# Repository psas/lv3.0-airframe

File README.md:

# PSAS Launch Vehicle 3 (LV3) 🚀

This is the repo for the LV3 airframe. This holds everything you need to know about making a rocket out of carbon fiber. This includes CAD files, design and prototyping logs, simulation and testing data, most of all the manufacturing procedures for the carbon fiber airframe modules.  

If you aren't allowed to push, send Joe or Andrew your Github username and ask for access. (This is different from getting added to the PSAS "organization".)

If you're looking to copy or build on this work check out the [doc directory](/doc/), especially the [layup procedure](/doc/mfg/moduleProcedure.md) and please message the people who have committed frequently/recently with any questions (or better yet, [make an issue with your question](https://github.com/psas/lv3.0-airframe/issues)).

If you want some quick physical specifications on the airframe, checkout the [quick facts.](doc/quickFacts.md)
For more detailed info, we have a [model](sim/ORK/LV3_L13.ork) for [OpenRocket](http://openrocket.info/) and a [model](cad/LV3.SLDASM) for [SolidWorks](http://www.solidworks.com/).

## Relevant Repositories
If you want to work on the CAD model, you'll need to have the dependencies cloned to the same directory as this repo. So, something like 

```
PSAS
├── lv3.0-airframe
├── lv3.0-recovery
├── lv3.0-camera-ring
├── lv3.0-umbilical-ring
├── sw-cad-airframe-nsr
└── reaction-control
```

You should also read the [Intro to Git workshop slides](https://drive.google.com/open?id=1pykfwvAw5q1oXGM8aLyhXPHOKDCI61YhK5w33QwzuFw) if you're new to Git
Also, read the [OreSat contributions guide](https://github.com/oresat/oresat-structure/blob/master/.github/CONTRIBUTING.md) if you're new to using SolidWorks with Git.

### Dependencies
* [psas/lv3.0-recovery](https://github.com/psas/lv3.0-recovery) -- CAD and analysis for the eNSR-based recovery system
* [psas/lv3.0-camera-ring](https://github.com/psas/lv3.0-camera-ring) -- 360 degree camera module based on the RunCam Split 2
* [psas/lv3.0-umbilical-ring](https://github.com/psas/lv3.0-umbilical-ring) -- passthrough module for the umbilical and arming switches (uses same format as camera ring)
* [psas/sw-cad-airframe-nsr](https://github.com/psas/sw-cad-airframe-nsr) -- Mechanical separation system for the nosecone/parachute
* [psas/reaction-control](https://github.com/psas/reaction-control) -- Cold gas reaction control system

### Historical
* [psas/LV3-design](https://github.com/psas/LV3-design) -- Early conceptual design of LV3
* [~~psas/mme-capstone~~](https://github.com/psas/mme-capstone) (**DEPRECATED**) -- One of the repositories created durring the 2014 capstone. This contains code for some of the tools they used. 
* [~~psas/sw-cad-carbon-fiber-process~~](https://github.com/psas/sw-cad-carbon-fiber-process) (**DEPRECATED**) -- Yet another repo from the 2014 team. This contains CAD for some of the tools they made.

## TODO:
[Check out the issues list if you're looking for something to do.](https://github.com/psas/lv3.0-airframe/issues) 
Keeping a TODO in the README never works out.

## Project Members
If you're working on the project in any way, please add yourself to this list.

IRL Name                       | Github username        | Current Role
------------------------------ | ---------------------- | ------------
Joe "Rocket Czar" Shields      | @Joedang               | project coordination; MFG; design
Leslie Elwood                  | @lelwood               | MFG; design; logistics
Alex "the Pretty Good" Farias  | @alexkazam             | MFG
Ian Zabel                      | @IanZabel              | cradle design; modelling
Kyle Blakeman                  | @kablakeman            | module sanding
Peter McCloud                  | @petermccloud          | CNC machining
Jorden Rolland                 | @JSRoland              | 
Katia                          | @kp07                  | 
Marie "Marie House" House      | @hmarie2               | anti-lithobreaking precautions
Adam Harris                    | @SaturnVF1             | MFG; manual machining
Josh Carlson                   | @paperman5             | CNC machining; design
Jacob Tiller                   | @JacobTiller           | machining; design
Erin Schmidt                   | @7deeptide             | system integration; design
Nathan Bergey                  | @natronics             | patron saint
Andrew Greenberg               | @andrewgreenberg       | benevolent dictator; pixie wrangler

## What and where
```
|-- cad						holds the Solidworks files for all the machined parts
│   ├── COTS					models for Commercial Off-The-Shelf parts
│   ├── CubeSatAirframeMount			"Cradle" that holds the flight computer (OreSat) inside LV3
|   |-- finCan
|	|-- LongFinFiles			current fin design (flyable and manufacturable)
|   |-- module					files for 18 and 24 inch modules
│   │   ├── jigs				jig for drilling side holes in module rings (and other radial parts)
│   │   └── layup
|   |-- nose					nosecone and mold subassemblies
|   |-- radome					radio-transparent fiberglass module
|   `-- railSled				part for interfacing with the launch rail
│       ├── CAM					G code for the rail sled (obsolete)
│       │   ├── Base
│       │   ├── Neck
│       │   └── Trunk
│       └── Old rail sled designs
|-- doc						all pure documentation
|   |-- aiaa-3.6.1				LaTeX template for AIAA
|   |-- extAbstract				extened abstract for the AIAA paper
|   |-- img					image resources for documentation
|   |-- mfg					step-by-step instructions for manufacturing
|   |-- paper					the conference paper we're submitting to AIAA Space
│   ├── FlightComputerMount			stuff about the Cradle
│   ├── textbook				summary of composite techniques in general
|   `-- updates					bi-monthlyish status updates on the project
|-- sim						simulations and calculations
|   |-- DATCOM					DATCOM cases for cross-validating the design (abandoned)
|   |   |-- case
|   |   |   |-- LV3				case for the LV3 airframe (not complete)
|   |   |   `-- exMiG
|   |   |-- doc					DATCOM documentation
|   |   `-- exlinux				example DATCOM cases
|   |-- ORK					open rocket models
|   |   `-- prev
|   |-- OpenFOAM				CFD models
|   |   `-- LV3\_LD-Haack			model of the 1:5 nose cone
|   |       `-- rcf_100				100-node-long mesh
|   |           |-- 0				initial conditions
|   |           |-- constant			fluid properites
|   |           `-- system			simulation parameters
|   |-- plots					plots of the open rocket data
|   |-- reductions				reductions of the openrocket simulations
|   `-- simData					output of the openrocket simulations
|-- test					data from physical tests on modules
|   `-- profilometer				surface roughness data
│   └── tinyMold				
└── tools					sources/CAD/docs for physical tools used to make LV3
    ├── Composite_Table				the table we do all the layups on
    ├── crusher-control				controller software for one of the crush testers at PSU	
    ├── oven-controller				the temperature controller for the oven
    │   ├── Oven_Controller			the temperature controller for... wait
    │   │   ├── Box				enclosure for the oven controller
    │   │   ├── OvenControl			the temperature contr-- again?!
    │   │   └── oven-controller-master		"A Deja Vu is usually a glitch in the Matrix."
    │   └── src					source code for the controller
    ├── Sheet_Cutting_Templates			templates used to cut sheets of CF, adhesive, et cetera
    └── strain-gauge-amplifier			instrument used to take strain measurements in a crush/tensile test
```

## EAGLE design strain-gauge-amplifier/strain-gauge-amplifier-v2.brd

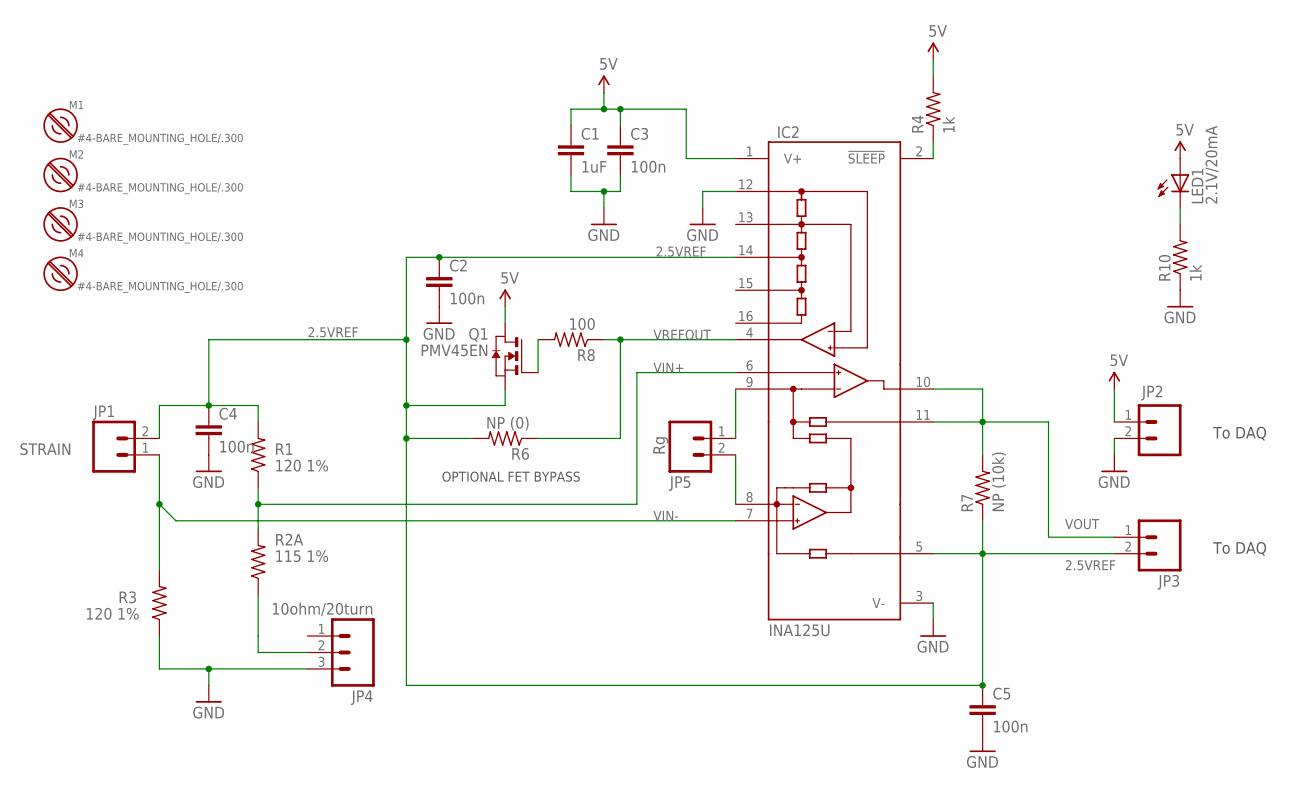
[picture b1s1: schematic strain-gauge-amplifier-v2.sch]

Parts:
C1: 1uF; 0805-C-NOSILK
C2, C3, C4, C5: 100n; 0805-C-NOSILK
IC2: INA125U; SO16-1
JP1: STRAIN; SCREWTERMINAL-5MM-2
JP2, JP3: M025MM; SCREWTERMINAL-5MM-2
JP4: 10ohm/20turn; 1X03_NO_SILK
JP5: Rg; SCREWTERMINAL-5MM-2
LED1: 2.1V/20mA; LED-0603
M1, M2, M3, M4: #4-BARE_MOUNTING_HOLE/.300; #4/.300-BARE+STD_NUT_OR_STAR_WASHER
Q1: PMV45EN; SOT23
R1, R3: 120 1%; 0805-C-NOSILK
R2A: 115 1%; 0805-C-NOSILK
R4, R10: 1k; 0805-C-NOSILK
R6: NP (0); 0805-C-NOSILK
R7: NP (10k); 0805-C-NOSILK
R8: 100; 0805-C-NOSILK

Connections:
2.5VREF: C2.1, C4.1, C5.1, IC2.5 (REF), IC2.14 (REF2.5), JP1.2, JP3.2, Q1.2 (S), R1.2, R6.2, R7.1
5V: C1.1, C3.1, IC2.1 (V+), JP2.1, LED1.A, Q1.3 (D), R4.2
GND: C1.2, C2.2, C3.2, C4.2, C5.2, IC2.3 (V-), IC2.12 (REFCOM), JP2.2, JP4.3, R3.1, R10.1
unnamed: JP4.2, R2A.1
unnamed: IC2.9 (RG), JP5.1
unnamed: IC2.8 (RG), JP5.2
unnamed: Q1.1 (G), R8.2
unnamed: IC2.2 (!SLEEP), R4.1
unnamed: LED1.C, R10.2
VIN+: IC2.6 (+IN), R1.1, R2A.2
VIN-: IC2.7 (-VIN), JP1.1, R3.2
VOUT: IC2.10 (OUT), IC2.11 (SENSE), JP3.1, R7.2
VREFOUT: IC2.4 (REFOUT), R6.1, R8.1

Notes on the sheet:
OPTIONAL FET BYPASS
To DAQ

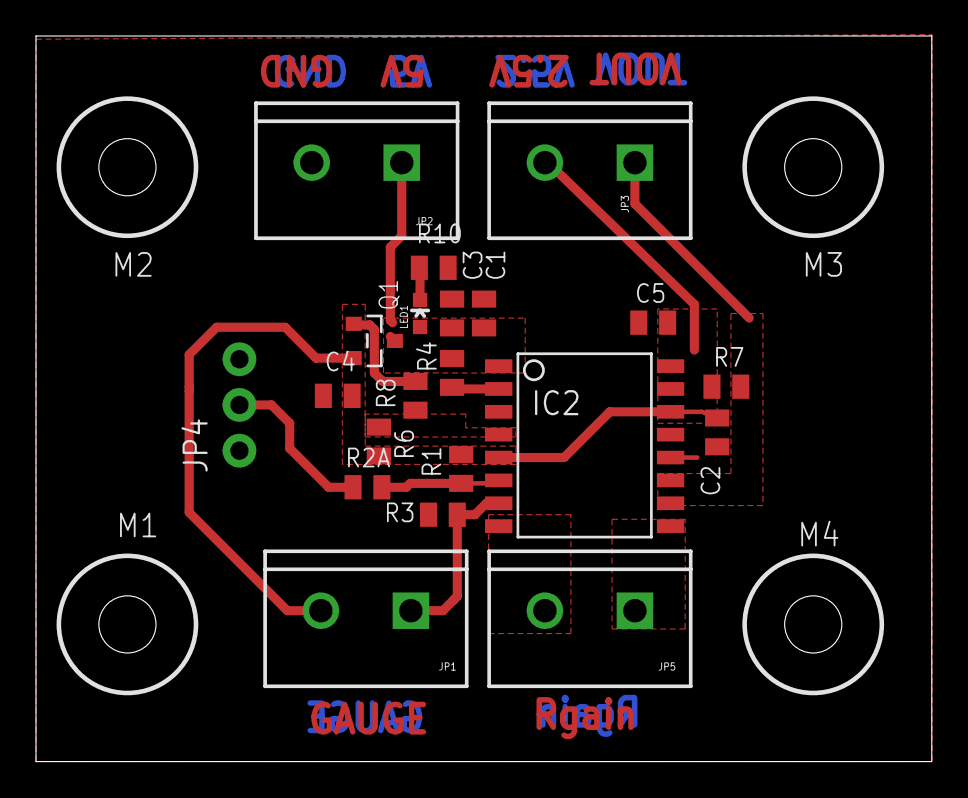
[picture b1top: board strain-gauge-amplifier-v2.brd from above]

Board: 2 copper layers, 49.8 x 40.3 mm, 25 parts (0 on the bottom side), 13 nets.

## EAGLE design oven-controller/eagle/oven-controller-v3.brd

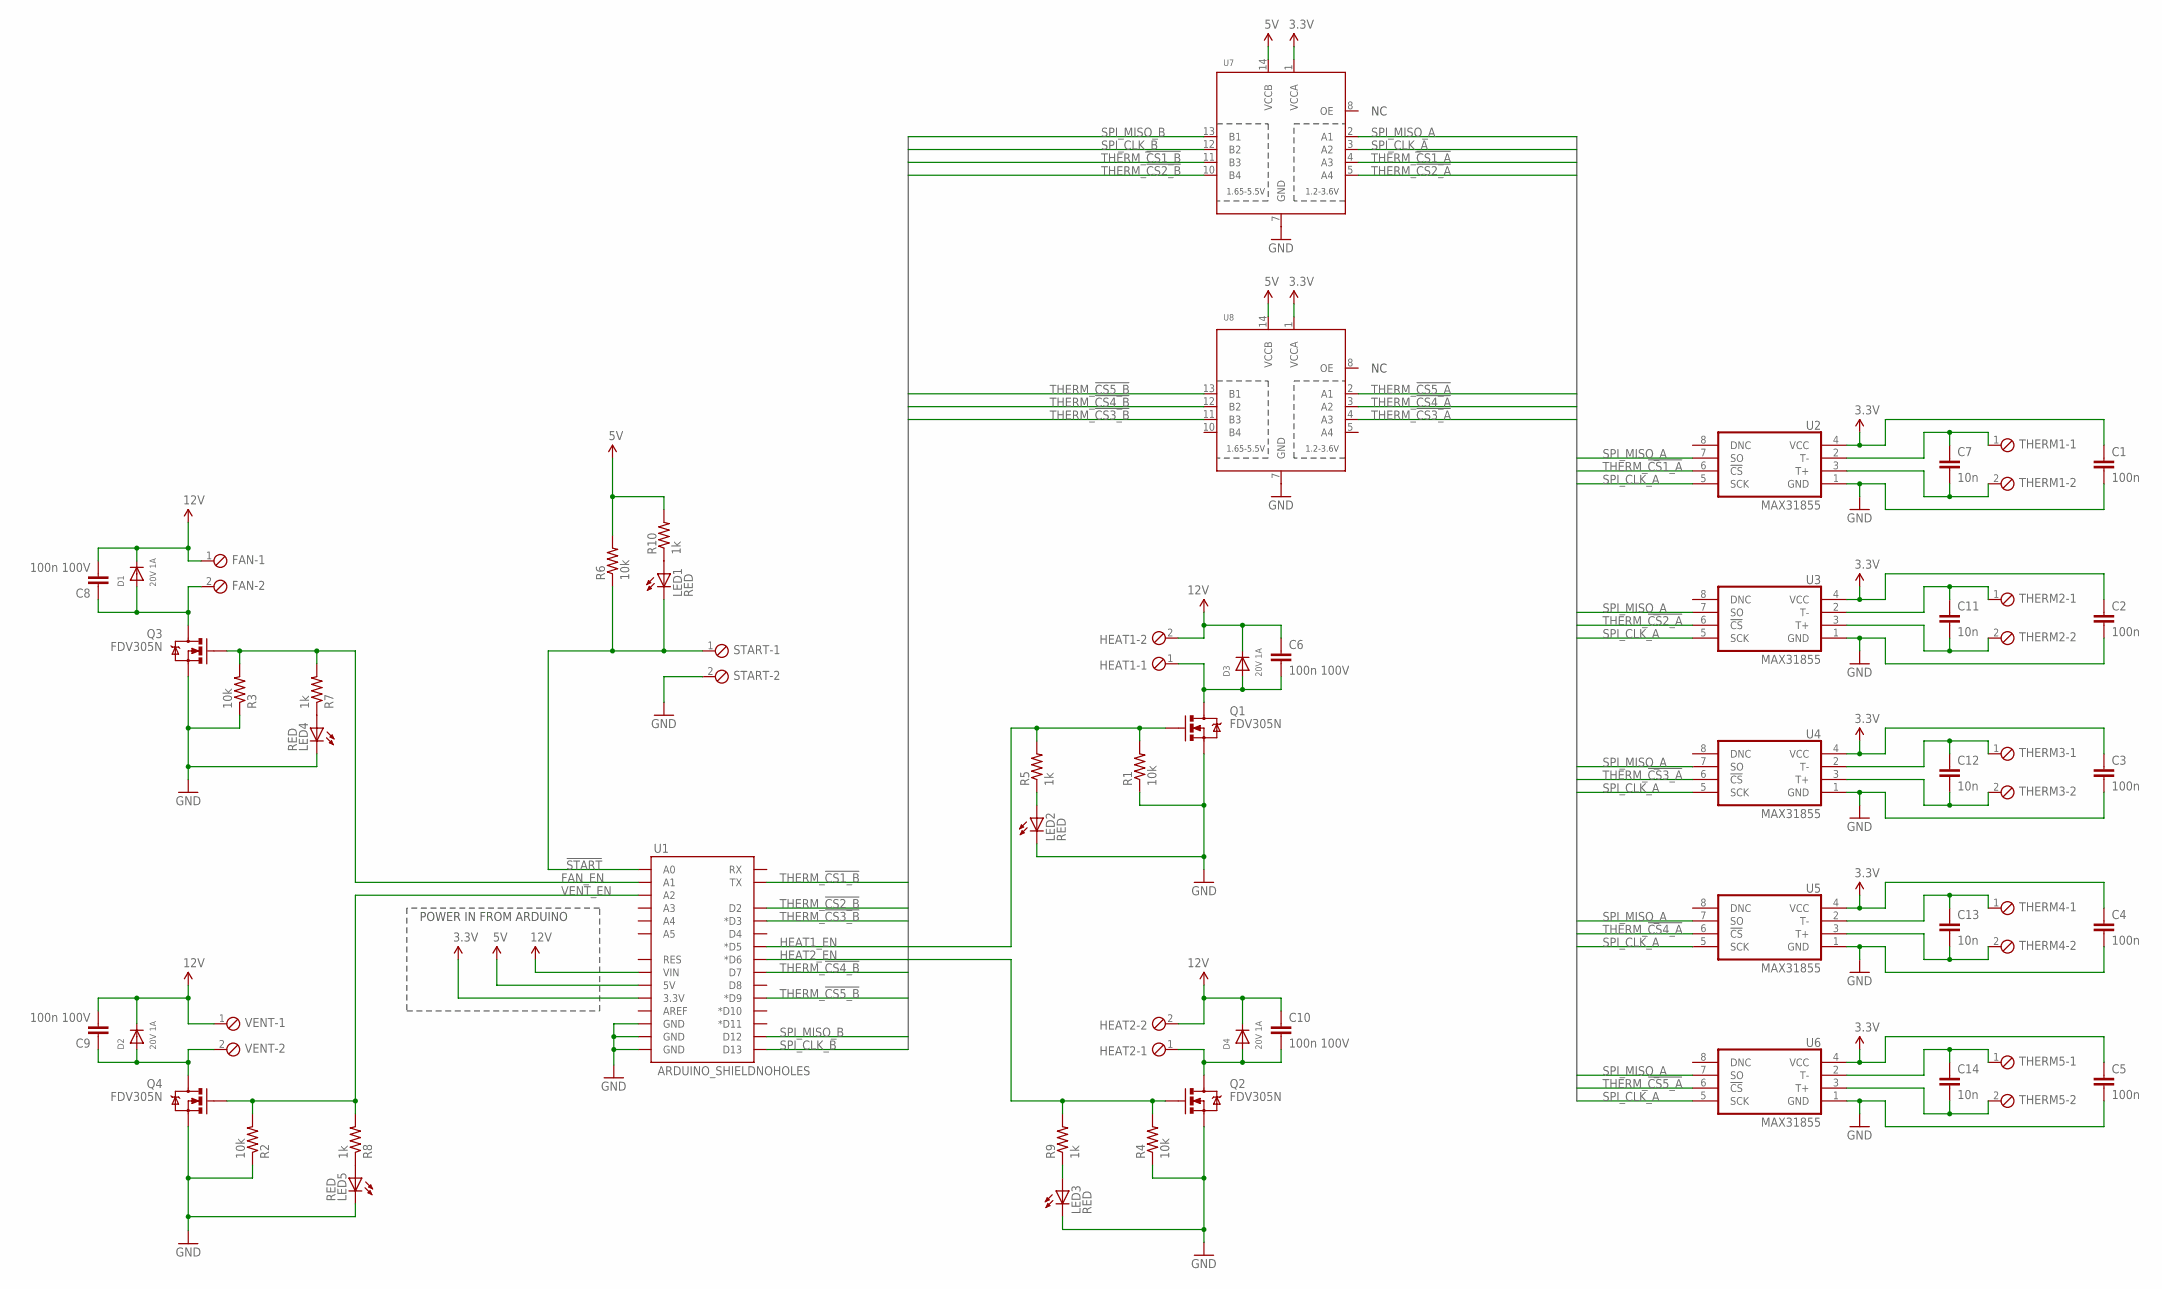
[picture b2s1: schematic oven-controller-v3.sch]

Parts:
C1, C2, C3, C4, C5: 100n; C0603K
C6, C8, C9, C10: 100n 100V; C0603K
C7, C11, C12, C13, C14: 10n; C0603K
D1, D2, D3, D4: 20V 1A; DO-214AC-SMA
FAN: MPT2; 2POL254
HEAT1, HEAT2: MPT2; 2POL254
LED1, LED2, LED3, LED4, LED5: RED; LED-0603
Q1, Q2, Q3, Q4: FDV305N; SOT23-3
R1, R2, R3, R4, R6: 10k; 0603-C-NOSILK
R5, R7, R8, R9, R10: 1k; 0603-C-NOSILK
START: MPT2; 2POL254
THERM1, THERM2, THERM3, THERM4, THERM5: MPT2; 2POL254
U1: ARDUINO_SHIELDNOHOLES; DUEMILANOVE_SHIELD_NOHOLES
U2, U3, U4, U5, U6: MAX31855; SO-8
U7, U8: TXB0104PWR; TSSOP14
VENT: MPT2; 2POL254

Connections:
3.3V: C1.1, C2.1, C3.1, C4.1, C5.1, U1.3.3V, U2.4 (VCC), U3.4 (VCC), U4.4 (VCC), U5.4 (VCC), U6.4 (VCC), U7.1 (VCCA), U7.8 (OE), U8.1 (VCCA), U8.8 (OE)
5V: R6.2, R10.2, U1.5V, U7.14 (VCCB), U8.14 (VCCB)
12V: C6.1, C8.2, C9.2, C10.1, D1.C, D2.C, D3.C, D4.C, FAN.1, HEAT1.2, HEAT2.2, U1.VIN, VENT.1
!START: LED1.C, R6.1, START.1, U1.A0
FAN_EN: Q3.1 (G), R3.2, R7.2, U1.A1
GND: C1.2, C2.2, C3.2, C4.2, C5.2, LED2.C, LED3.C, LED4.C, LED5.C, Q1.2 (S), Q2.2 (S), Q3.2 (S), Q4.2 (S), R1.1, R2.1, R3.1, R4.1, START.2, U1.GND@0 (GND), U1.GND@1 (GND), U1.GND@2 (GND), U2.1 (GND), U3.1 (GND), U4.1 (GND), U5.1 (GND), U6.1 (GND), U7.7 (GND), U8.7 (GND)
HDR3: C8.1, D1.A, FAN.2, Q3.3 (D)
HEAT1_EN: Q1.1 (G), R1.2, R5.2, U1.D5 (*D5)
HEAT2_EN: Q2.1 (G), R4.2, R9.2, U1.D6 (*D6)
unnamed: LED1.A, R10.1
unnamed: C7.1, THERM1.1, U2.2 (T-)
unnamed: C9.1, D2.A, Q4.3 (D), VENT.2
unnamed: C6.2, D3.A, HEAT1.1, Q1.3 (D)
unnamed: C7.2, THERM1.2, U2.3 (T+)
unnamed: C13.1, THERM4.1, U5.2 (T-)
unnamed: LED2.A, R5.1
unnamed: C13.2, THERM4.2, U5.3 (T+)
unnamed: LED4.A, R7.1
unnamed: C12.1, THERM3.1, U4.2 (T-)
unnamed: C11.1, THERM2.1, U3.2 (T-)
unnamed: C11.2, THERM2.2, U3.3 (T+)
unnamed: C14.2, THERM5.2, U6.3 (T+)
unnamed: C14.1, THERM5.1, U6.2 (T-)
unnamed: LED3.A, R9.1
unnamed: LED5.A, R8.1
unnamed: C12.2, THERM3.2, U4.3 (T+)
unnamed: C10.2, D4.A, HEAT2.1, Q2.3 (D)
SPI_CLK_A: U2.5 (SCK), U3.5 (SCK), U4.5 (SCK), U5.5 (SCK), U6.5 (SCK), U7.3 (A2)
SPI_CLK_B: U1.D13, U7.12 (B2)
SPI_MISO_A: U2.7 (SO), U3.7 (SO), U4.7 (SO), U5.7 (SO), U6.7 (SO), U7.2 (A1)
SPI_MISO_B: U1.D12, U7.13 (B1)
THERM_!CS1_A: U2.6 (!CS), U7.4 (A3)
THERM_!CS1_B: U1.TX, U7.11 (B3)
THERM_!CS2_A: U3.6 (!CS), U7.5 (A4)
THERM_!CS2_B: U1.D2, U7.10 (B4)
THERM_!CS3_A: U4.6 (!CS), U8.4 (A3)
THERM_!CS3_B: U1.D3 (*D3), U8.11 (B3)
THERM_!CS4_A: U5.6 (!CS), U8.3 (A2)
THERM_!CS4_B: U1.D7, U8.12 (B2)
THERM_!CS5_A: U6.6 (!CS), U8.2 (A1)
THERM_!CS5_B: U1.D9 (*D9), U8.13 (B1)
VENT_EN: Q4.1 (G), R2.2, R8.2, U1.A2

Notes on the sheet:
POWER IN FROM ARDUINO

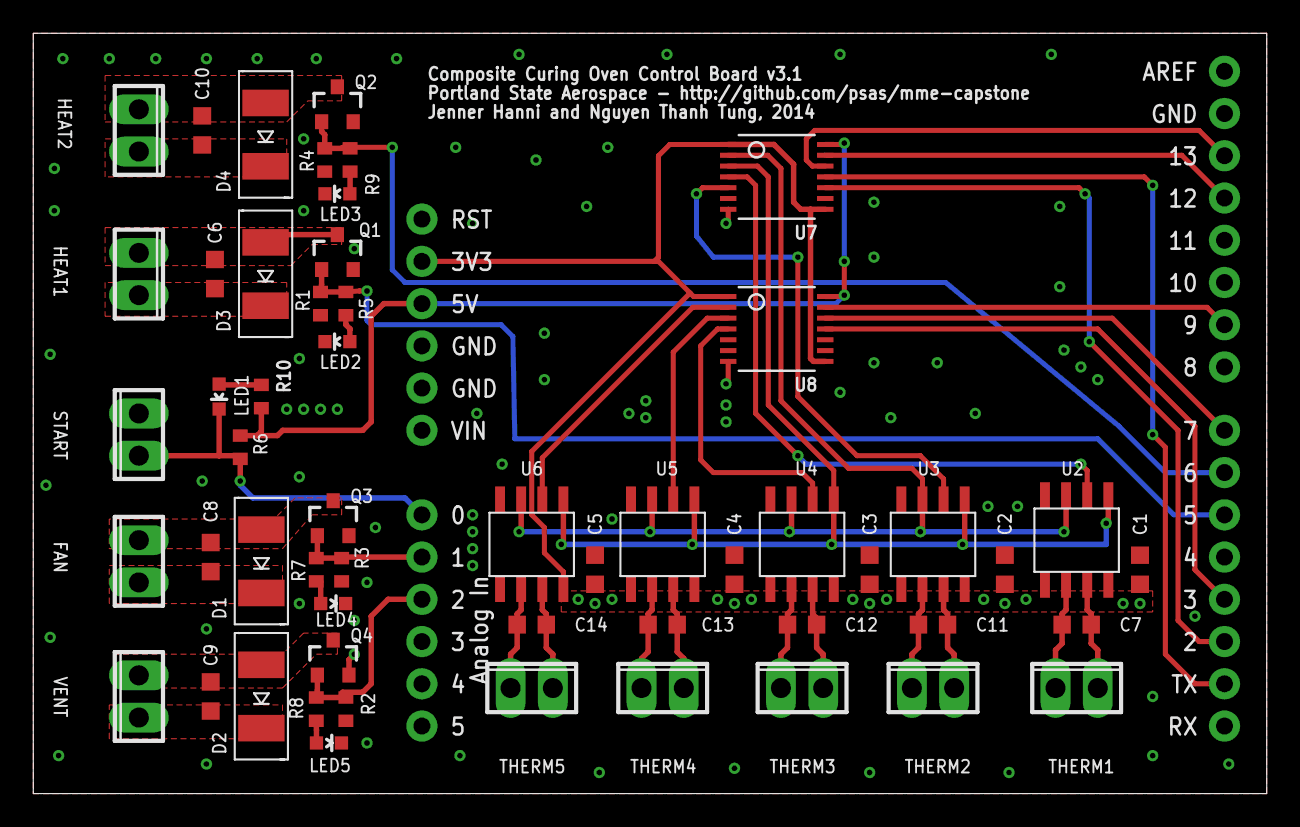
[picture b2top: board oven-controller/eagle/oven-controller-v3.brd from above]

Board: 2 copper layers, 74.2 x 45.7 mm, 55 parts (0 on the bottom side), 42 nets.

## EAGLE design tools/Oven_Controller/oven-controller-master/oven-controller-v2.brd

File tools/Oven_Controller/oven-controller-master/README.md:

oven-controller
===============

For the composites oven team at Portland State. 

v0 - the original schematic representation of the current working breadboard setup.

v1 - the finished Arduino shield version on a printed circuit board. this works! 

v2 - additions to the v1 Arduino shield design

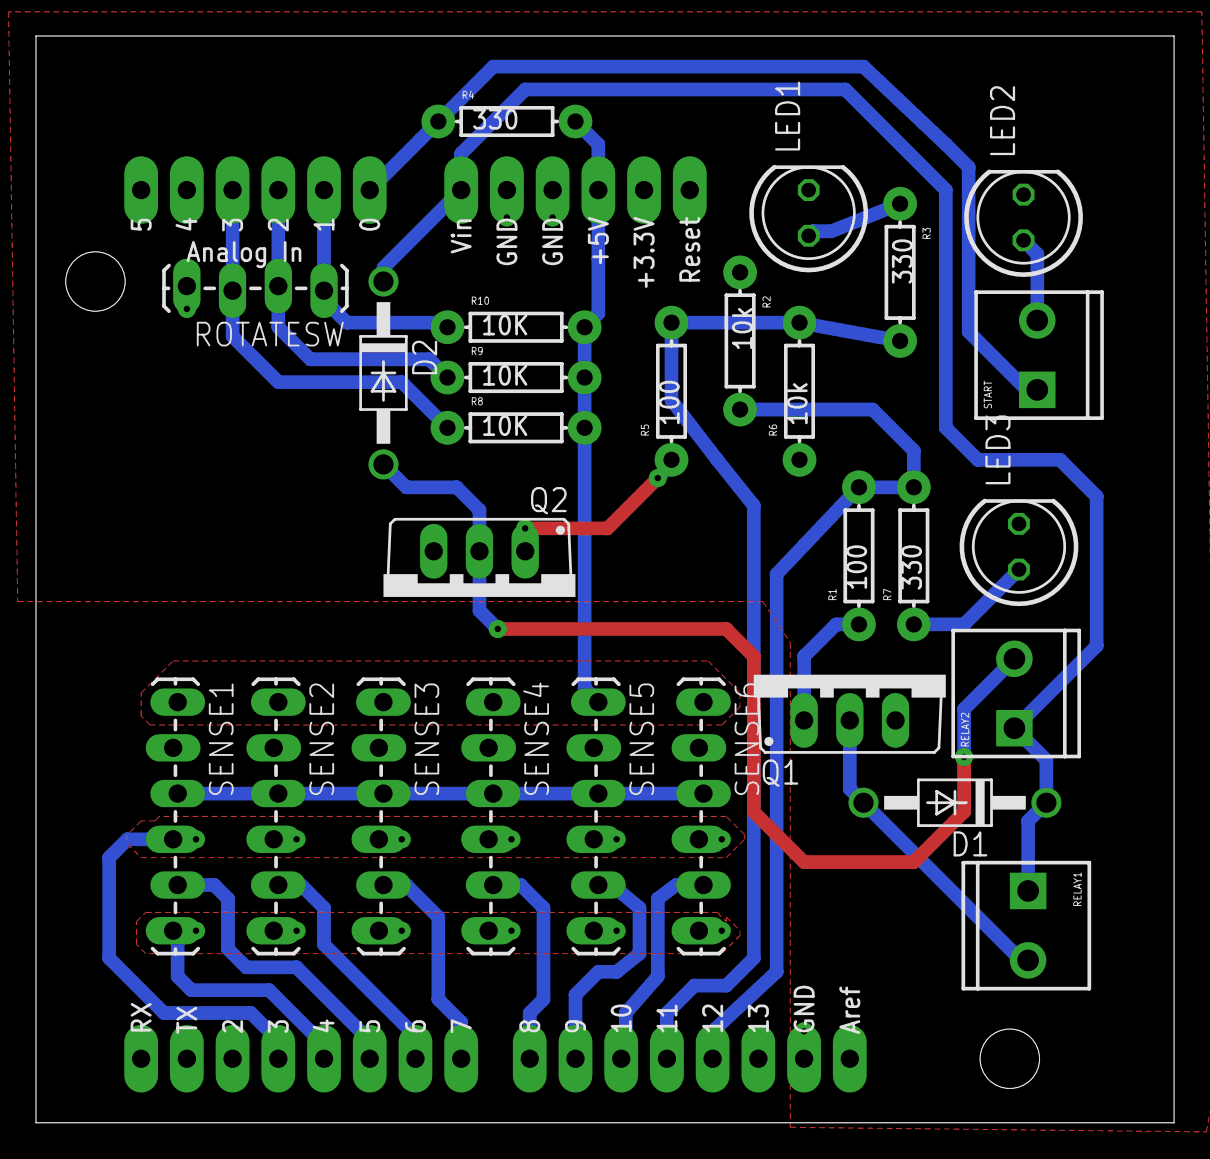
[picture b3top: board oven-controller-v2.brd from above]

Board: 2 copper layers, 63.2 x 60.4 mm, 28 parts (0 on the bottom side), 24 nets.

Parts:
D1, D2: 1N4942; DO41-10
LED1, LED2, LED3: RED; LED5MM
Q1, Q2: IRFL310; TO220BV
R1, R5: 100; AXIAL-0.3
R2, R6: 10k; AXIAL-0.3
R3, R4, R7: 330; AXIAL-0.3
R8, R9, R10: 10K; AXIAL-0.3
RELAY1: RL1; SCREWTERMINAL-3.5MM-2_LOCK
RELAY2: RL2; SCREWTERMINAL-3.5MM-2_LOCK
ROTATESW: SW; 1X04_LOCK_LONGPADS
SENSE1, SENSE2, SENSE3, SENSE4, SENSE5, SENSE6: 1X06_LOCK_LONGPADS
START: SCREWTERMINAL-3.5MM-2_LOCK
U1: ARDUINO_SHIELDLONGPADS; DUEMILANOVE_SHIELD_LONGPADS

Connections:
5V: R4.P$2, R8.P$2, R9.P$2, R10.P$2, SENSE1.1, SENSE2.1, SENSE3.1, SENSE4.1, SENSE5.1, SENSE6.1, U1.5V
A0: R4.P$1, START.1, U1.A0
A1: R10.P$1, ROTATESW.1, U1.A1
A2: R9.P$1, ROTATESW.2, U1.A2
A3: R8.P$1, ROTATESW.3, U1.A3
CCO: SENSE1.4, SENSE2.4, SENSE3.4, SENSE4.4, SENSE5.4, SENSE6.4, U1.D3
CS_PIN5: SENSE1.5, U1.D5
CS_PIN6: SENSE2.5, U1.D6
CS_PIN7: SENSE3.5, U1.D7
CS_PIN8: SENSE4.5, U1.D8
CS_PIN9: SENSE5.5, U1.D9
CS_PIN10: SENSE6.5, U1.D10
CS_PIN11: R3.P$2, R5.P$2, R6.P$2, U1.D11
CS_PIN12: R1.P$2, R2.P$2, R7.P$2, U1.D12
GND: LED1.K, LED2.K, LED3.K, Q1.S, Q2.S, R2.P$1, R6.P$1, ROTATESW.4, SENSE1.3, SENSE2.3, SENSE3.3, SENSE4.3, SENSE5.3, SENSE6.3, U1.GND@0, U1.GND@1, U1.GND@2
unnamed: Q2.G, R5.P$1
unnamed: Q1.G, R1.P$1
unnamed: D1.A, Q1.D, RELAY1.2
unnamed: D2.A, Q2.D, RELAY2.2
unnamed: LED1.A, R3.P$1
unnamed: LED3.A, R7.P$1
unnamed: LED2.A, START.2
SCLK_PIN4: SENSE1.6, SENSE2.6, SENSE3.6, SENSE4.6, SENSE5.6, SENSE6.6, U1.D4
VIN: D1.C, D2.C, RELAY1.1, RELAY2.1, U1.VIN

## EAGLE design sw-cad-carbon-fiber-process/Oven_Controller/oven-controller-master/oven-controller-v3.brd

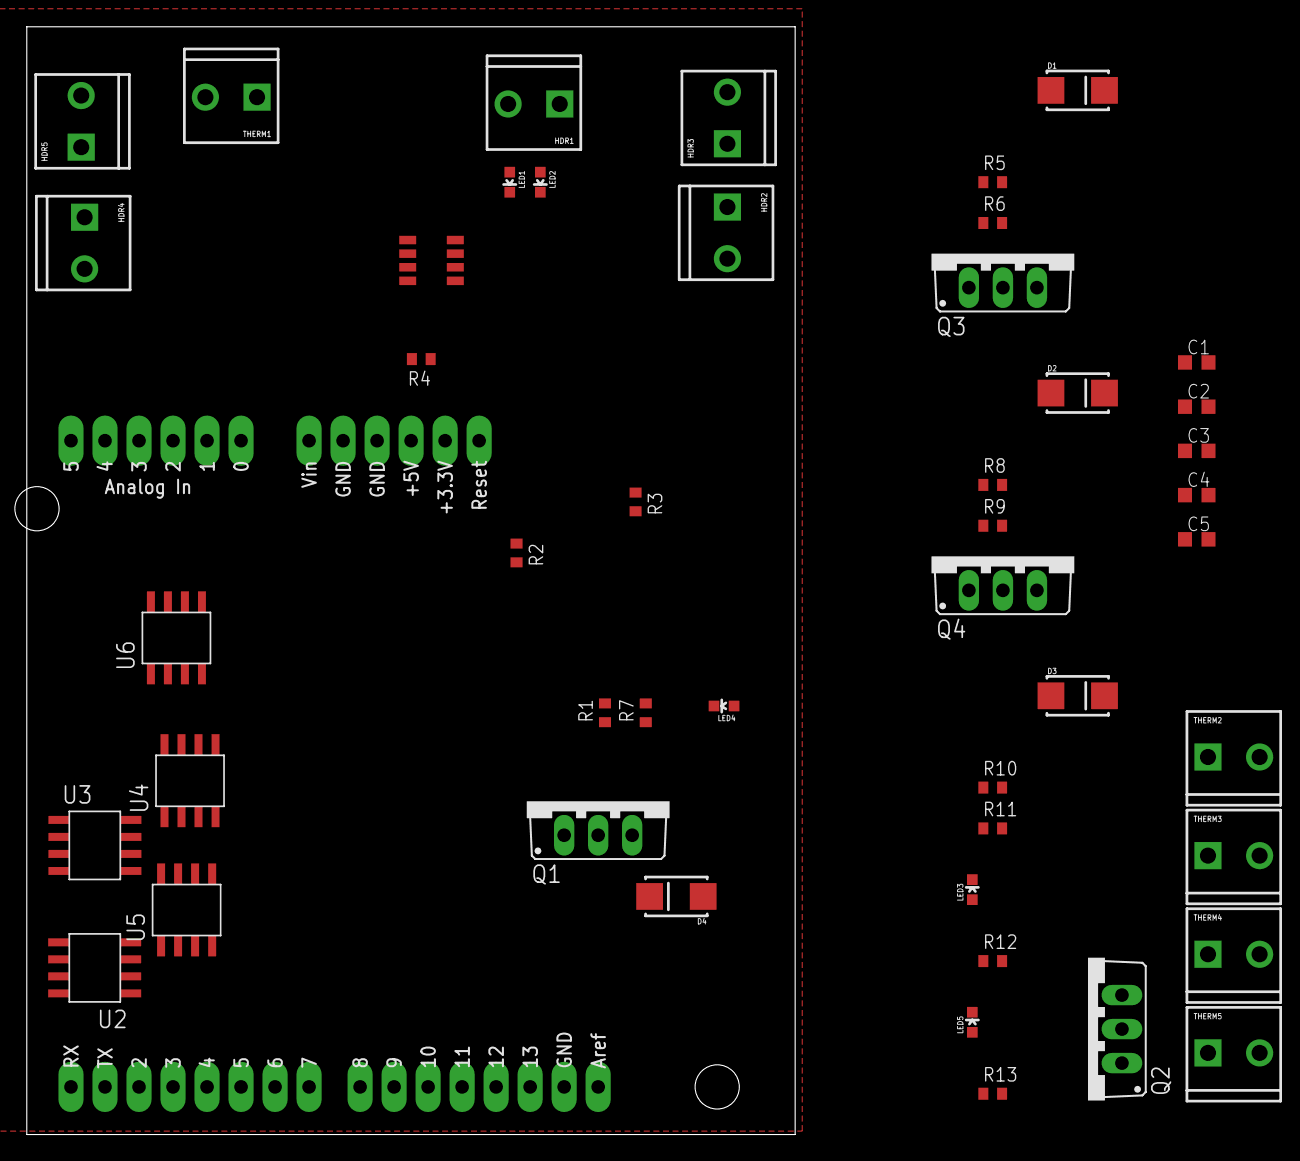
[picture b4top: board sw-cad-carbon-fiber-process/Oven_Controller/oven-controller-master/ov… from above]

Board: 2 copper layers, 57.4 x 82.7 mm, 48 parts (0 on the bottom side), 39 nets, no tracks yet.

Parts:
C1, C2, C3, C4, C5: C0603K
D1, D2, D3, D4: RS1DB-13-F; SMA-DIODE_ALT
HDR1: SCREWTERMINAL-3.5MM-2_LOCK
HDR2: HEAT1; SCREWTERMINAL-3.5MM-2_LOCK
HDR3: HEAT2; SCREWTERMINAL-3.5MM-2_LOCK
HDR4: FAN; SCREWTERMINAL-3.5MM-2_LOCK
HDR5: VENT; SCREWTERMINAL-3.5MM-2_LOCK
LED1, LED2, LED3, LED4, LED5: RED; LED-0603
Q1, Q2, Q3, Q4: IRFL310; TO220BV
R1, R5, R8, R10: 100; 0603-C-NOSILK
R2, R6, R9, R11: 10k; 0603-C-NOSILK
R3, R4, R7, R12, R13: 330; 0603-C-NOSILK
THERM1, THERM2, THERM3, THERM4, THERM5: SCREWTERMINAL-3.5MM-2_LOCK
U1: ARDUINO_SHIELDLONGPADS; DUEMILANOVE_SHIELD_LONGPADS
U2, U3, U4, U5, U6: MAX31855; SO-8
U7: SN74LVC1G139; 8LSSOP

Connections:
3.3V: C1.1, C2.1, C3.1, C4.1, C5.1, U1.3.3V, U2.4, U3.4, U4.4, U5.4, U6.4
5V: R4.2, U1.5V, U7.P$8
12V: D1.C, D2.C, D3.C, D4.C, HDR2.1, HDR3.1, HDR4.1, HDR5.1, U1.VIN
CS_FAN: R7.2, R10.2, R11.2, U7.P$5
CS_HEAT1: R3.2, R5.2, R6.2, U7.P$7
CS_HEAT2: R8.2, R9.2, R12.2, U7.P$6
CS_VENT: R1.2, R2.2, R13.2, U7.P$3
GND: C1.2, C2.2, C3.2, C4.2, C5.2, LED1.C, LED2.C, LED3.C, LED4.C, LED5.C, Q1.S, Q2.S, Q3.S, Q4.S, R2.1, R6.1, R9.1, R11.1, U1.GND@0, U1.GND@1, U1.GND@2, U2.1, U3.1, U4.1, U5.1, U6.1, U7.P$4
HDR3: D3.A, HDR4.2, Q4.D
unnamed: Q2.G, R5.1
unnamed: Q1.G, R1.1
unnamed: D4.A, HDR5.2, Q1.D
unnamed: D1.A, HDR2.2, Q2.D
unnamed: THERM1.1, U2.2
unnamed: THERM1.2, U2.3
unnamed: LED2.A, R3.1
unnamed: THERM2.1, U3.2
unnamed: LED4.A, R7.1
unnamed: HDR1.2, LED1.A
unnamed: THERM2.2, U3.3
unnamed: THERM3.1, U4.2
unnamed: THERM3.2, U4.3
unnamed: THERM4.1, U5.2
unnamed: THERM4.2, U5.3
unnamed: THERM5.1, U6.2
unnamed: THERM5.2, U6.3
unnamed: LED3.A, R12.1
unnamed: LED5.A, R13.1
unnamed: Q3.G, R8.1
unnamed: D2.A, HDR3.2, Q3.D
unnamed: Q4.G, R10.1
RELAY_MUX_SEL1: U1.D5, U7.P$1
RELAY_MUX_SEL2: U1.D6, U7.P$2
START: HDR1.1, R4.1, U1.A0
THERM_CS1: U1.TX, U2.6
THERM_CS2: U1.D2, U3.6
THERM_CS3: U1.D3, U4.6
THERM_CS4: U1.D7, U5.6
THERM_CS5: U1.D9, U6.6

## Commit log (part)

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2016-02-25 added to Significance and Plan of Work
2016-02-25 removed reference to other teams using PSAS designs
2016-03-04 added nose heating analysis script
2016-03-13 optimized spline point placement
    This script is meant to find the optimal placement of an extra spline point for the LV3 nose cone. The curvature of the LD-Haack shape near the tip creates a large error when using evenly distributed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
2016-03-30 Experimented with fin shapes. Started DATCOM input.
2016-03-31 Added neutrally stable fin design.
2016-03-31 added very rough model for L13b
2016-04-01 output files for the MiG-17 case
2016-04-01 silly to have huge DATCOM source messing up commit logs
2016-04-01 updated description
2016-04-03 added symmetrical fin version
2016-04-12 fixed wrong image name
2016-04-12 wrote more of the update, added images
2016-04-15 finished writing the "weekly" update
2016-04-15 minor edits to the weekly update
2016-05-09 wrote another update
2016-05-20 added directory for AIAA paper, and did some prep
2016-05-23 profilometer stuff; will add other data soon.
2016-05-26 added a CoP compensation design that uses 4 fins (not worth it)
    The apogee is basically the same and it uses an extra fin. There's not
    much point to this.
2016-06-11 Wrote the fin layup procedure; modified cylinder layup
    The fin procedure still needs images. The cylinder layup needs updated
    images.
2016-06-15 slight documentation reorganization
2016-06-16 fixed to-do list formatting
2016-06-18 Update README.md
    My apologies for the mess. I was just practicing different things from a work computer and I didn't realize it was creating a problem (?).
2016-06-22 Cleared out the old cad files
2016-06-23 Readme: Clean up some markup for readability.
2016-07-06 Changed material definition; modified truss size; added composite thickness
2016-07-07 Added fillet, updated drag force, applied mesh control, next step: weight reduction
2016-07-11 added pics for layup tutorial and mold sealing
2016-07-16 Added new new fin design with slot for leading edge material
2016-07-19 Added temp markdown for flutter velocity calculation
2016-07-20 modified nose mold to accommodate recovery system
    increased the cylindrical section from 2 in to 8 in
    increased the nose hole diameter to 1 in
    made a slight change in the defining dimensions of the nose tip
2016-07-25 Strengthened front/back of mold; added index holes; added a ruler
2016-07-29 most of the modifications requested by Alex Chally
    still need to add indexing holes, fixturing holes, and optional flange
    holes
2016-07-30 Updated the fin CAD
2016-07-30 found a *good* solution to show the analysis
    ... after a lot of fighting with pandoc ;_;
2016-07-30 updated the model, as per Allex Chally's requests
2016-08-02 added descriptions on open-source software used
2016-08-03 added crush data for LU16-20 (fiberglass module)
2016-08-03 renamed the crush analysis; added the plots
2016-08-08 Added to the nose cone section
2016-08-09 added BOM from 2014 version
2016-08-12 description of the basic design and bibliography
    Next:
    add diagram/picture of the sandwich design;
    add more detailed description of the modules
    add pictures of the compressive failure
    add pictures of the puncture failure
    add CAD render of the cylindrical modules and/or whole rocket (this
2016-08-14 added materials and module sections, layer diagram
    Next:
    add pictures of descructive testing
    add picture of layers, put alongside diagram
    add picture/model of module
    write section on destructive testing
    add plot of surface features
2016-08-16 Add to aquire and nose cone 8/15
2016-08-17 some figure fixes
    Also checking to see if my local copy still points to the remote one
2016-08-18 some figure changes; changed testing and nose cone
2016-08-18 condensed NC and MAT sections; moved figures
2016-08-18 merged redundant paragraphs
2016-08-18 PSAS is plans -> PSAS' plans
2016-08-19 Updated sheet metal model; Edited assembly
2016-08-24 Updated old assembly, added polycarbonate model
2016-08-27 Added LV3 fin jigs
2016-08-30 Updated plexi assembly; Created necessary components and assembly
2016-09-02 Updated acrylic model; Added drawings; Added telem placeholder
2016-09-07 added some pics of the taping/bagging process
2016-09-08 This piece attaches the cubesat cradle to the module rings.
2016-09-08 found a decent way to get tables into Inkscape
2016-09-09 added plots to the poster
2016-09-09 added dummy text and did some alignment tweaking
2016-09-10 Added end plate laser cutting sheet
2016-09-10 added actual text; changed QR codes; tweaked fonts
2016-09-12 Added more exposition and updated requirements.
2016-09-13 Updated requirements text
2016-09-25 Technical drawing for nose cone tip.
2016-09-27 added MasterCAM coordinate system to the model
2016-09-28 Added even more laser cutting files; Added the new rail to be cut
2016-10-10 Created sim assembly and part, performed static torsion sim
2016-10-12 Updated V2 Assem; Included V2 CubeSat (2U); Modified Interface ring for strength and weight
2016-10-18 updated README; created SLDPRT of a test mold
2016-10-20 Updated middle fin jig technical drawing
2016-10-24 Made a technical drawing for the top/bottom fin jigs
2016-11-07 added initial files for fin CAM
2016-12-13 Updated mid fin jig drawing and redid top/bottom fin jig drawing
2016-12-18 added the RCS ring to the main assembly
    Still need to add :
    * guts for the RCS
    * guts for the eNSR
    * recovery system
    * motor
    We (PSAS) should also try to figure out some way of saving our SW
2016-12-21 Updated fin jig drawings to be more standardized
2017-01-10 possible geometry for the big mold
    used to make a negative mold with carbon fiber
2017-01-10 updated BOM to 2016 version
2017-01-13 Updated README to provide suggested reading.
2017-02-09 added images of the layup process and the molds
    I also made a python script to convert images to a smaller size.
    If an image is larger than 500 pickles in both dimensions, it
    rescales the image to be 500 pickles in the smallest dimension.
    That should be a bit easier than doing each one in GIMP.
2017-02-13 updated module MFG procedure and README
2017-02-22 added relevant repos to README
2017-02-25 extra debugging to the serial monitor
2017-02-27 added picture and video of the nosecone mold layup
2017-03-27 small tweaks to the tip drawing
2017-03-28 Updated TODO
2017-03-30 tweaked coordinate system
2017-03-30 technical drawing for the fin jig baseplate
2017-04-05 assemblies/parts for making/using nosecone mold
2017-04-06 created technical drawing of the sled jig
2017-04-11 created drawing of male coupling ring
2017-04-11 explanatory drawing of how internals mount to LV3
    Needs screws!
2017-04-15 embiggened registration marks
2017-04-17 integrated documents from CF-process
2017-04-17 reorganized/renamed files to conform to repo style
2017-04-17 Github-ized the carbon fiber textbook
    pandoc CarbonFiberDesignTextbook.md -t markdown_github \
    -o CarbonFiberDesignTextbook2.md
2017-04-18 Added cradle sub-assembly; Pointed assembly to correct files
2017-05-08 some calculations to find loading at root of fin
2017-05-12 Added Moment of Inertia and bolt shear calculations
2017-05-16 Double checked bolt shear / Moments of Inertia
2017-05-18 tried fixing the LV3 DATCOM input again
    Still getting NaN for drag, lift, etc. on the body.
2017-05-22 Tied cradle to oresat/structure WARNING: not for puny computers currently
2017-05-23 removed old shell and tip
    Need to go through and identify remaining old files...
2017-05-27 3D-printable spider for the module sanding
2017-05-31 OpenRocket case and R notebook for double eNSR
2017-06-02 Found the problem in the DATCOM model! (kinda)
    It's something to do with the station-wise definition of the body not
    working at high Mach numbers. DATCOM gives normal outputs for the model
    at low Mach numbers, but it poops out at high (~1.5) Mach numbers.
    It also doesn't seem to like the altitudes being specified in inches,
    which is annoying. I'm not sure if changing the dimensions into feet
    would help. It would be a pain to do though... I'm not sure if it would
2017-06-03 corrected rounding/legacy errors in DATCOM input
    I used the `y()` function in
    `sim/OpenFOAM/LV3_LD-Haack/noseSplineOptimizer.R` (modified to units of
    inches, of course) to correct rounding errors in the postions and areas
    of the body stations.
    I compared to the OpenRocket model to double-check the
    dimensions/locations of the fins and the overall length of the rocket.
2017-06-04 Updated geometry to match physical model
2017-06-07 redoing previous work on parsing OpenRocket output
    Also remembering which functions are most useful in R, lol.
2017-06-12 further tweaking to R notebook and DATCOM model
    At first glance, the drag coefficients from OpenRocket and DATCOM seem
    to wildly disagree...
    OH MY GOD
    EVERYTHING IS TERRIBLE
    WHY AM I SPENDING MY TIME THIS WAY
    THIS IS SO TEDIOUS
2017-06-13 calculated fin loading in the supersonic regime
    Still need to calculate subsonic and transonic loading...
2017-06-24 started nosecone process documentation
2017-07-24 Add files via upload
    Files for the bolt-down fin jig clamp bolt mounts.
2017-09-06 added in a bunch of 3D printable specialty tools
2017-09-27 Added fasteners to the coupling example
    McMaster-Carr models of the fasteners are now included in cad/COTS.
    The fasteners appear in both the assembly and the drawing. Labels have
    been added to the drawing, indicating the necessary dimensions of the
    fasteners. The PDF of the drawing has also been re-rendered.
2017-10-28 modular version of the jigs
2017-10-28 started mounts for spiders
2017-10-28 single-rail version of the spine
2017-10-30 generic ring to use as a reference
    If someone needs to create a ring that has access to the air stream,
    they should start from this.
2017-11-03 hole for telemetrum antenna; optional mount holes
2017-11-29 added COTS drill collars to drill steadies
2017-12-13 added collars to all hole steadies
    Still need to make the collar part for the 0.1285" hole (trivial).
2017-12-27 added info about the first nosecone attempt
2018-01-05 removed old script
2018-01-06 reorganized assembly for review
2018-01-20 updated OR model with physical mass measurements
2018-02-20 mass cutouts for bulkhead; simple mounting
2018-02-20 OMG, we're dumb.
    The camera ring is in a separate repo now. Go there instead!
    https://github.com/psas/lv3.0-camera-ring
2018-03-01 made README more readable; tidied root of repo
2018-03-23 renamed cradle directory
2018-03-23 fixed cosmetics
2018-03-24 lots of routing holes in the cradle
2018-04-17 initial foam packing plans for airframe
2018-04-18 finalized templates; prepared laser file
2018-04-24 refined OR model from scrubbed April L-13 launch
2018-04-25 assembled first draft of rail button
2018-04-30 hard point that can go between rings
2018-04-30 finalized drawing of the button ring
2018-05-08 updated OR model with rail button rings
2018-05-11 drawing of rail button
2018-05-13 CAD for a safety cover for the nosecone tip
2018-05-15 FDM-able tip safety; missing dimension on ballast
2018-06-18 cleaned up the module procedure before workshop

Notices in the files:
parts and their libraries:
SparkFun-Boards: Licensing: CC v3.0 Share-Alike You are welcome to use this library for commercial purposes.
SparkFun-DigitalIC: Licensing: Creative Commons ShareAlike 4.0 International - https://creativecommons.org/licenses/by-sa/4.0
